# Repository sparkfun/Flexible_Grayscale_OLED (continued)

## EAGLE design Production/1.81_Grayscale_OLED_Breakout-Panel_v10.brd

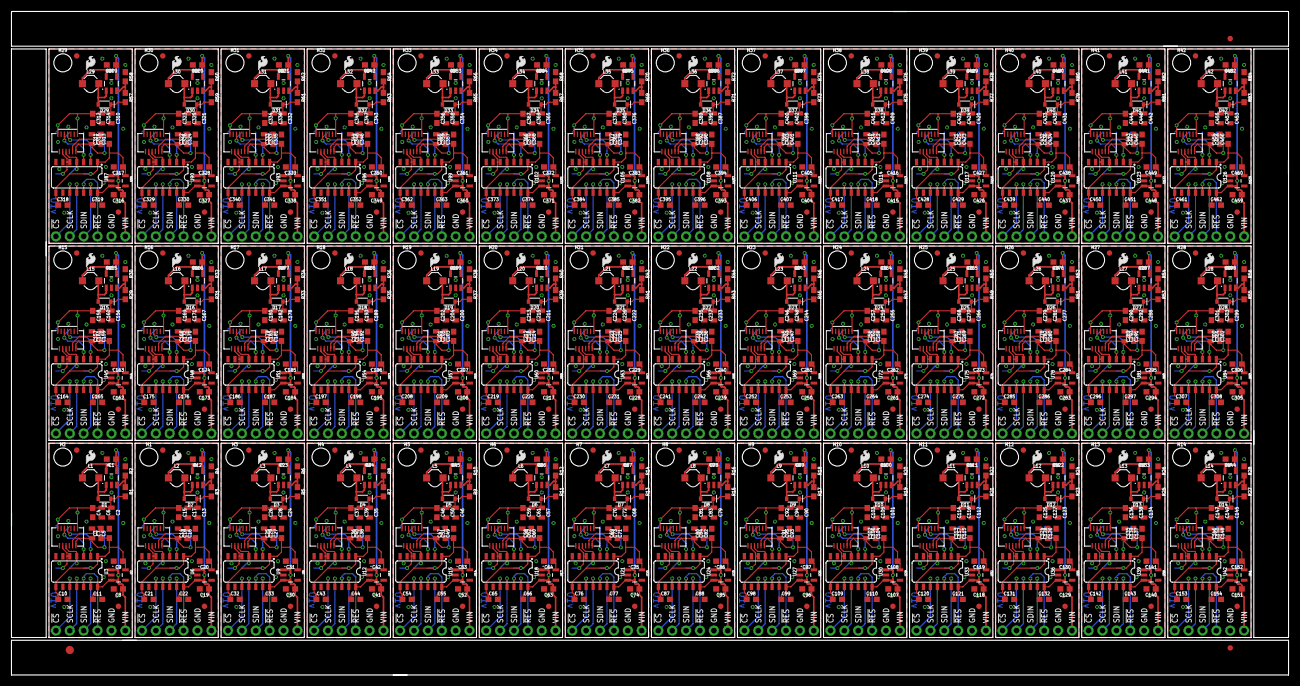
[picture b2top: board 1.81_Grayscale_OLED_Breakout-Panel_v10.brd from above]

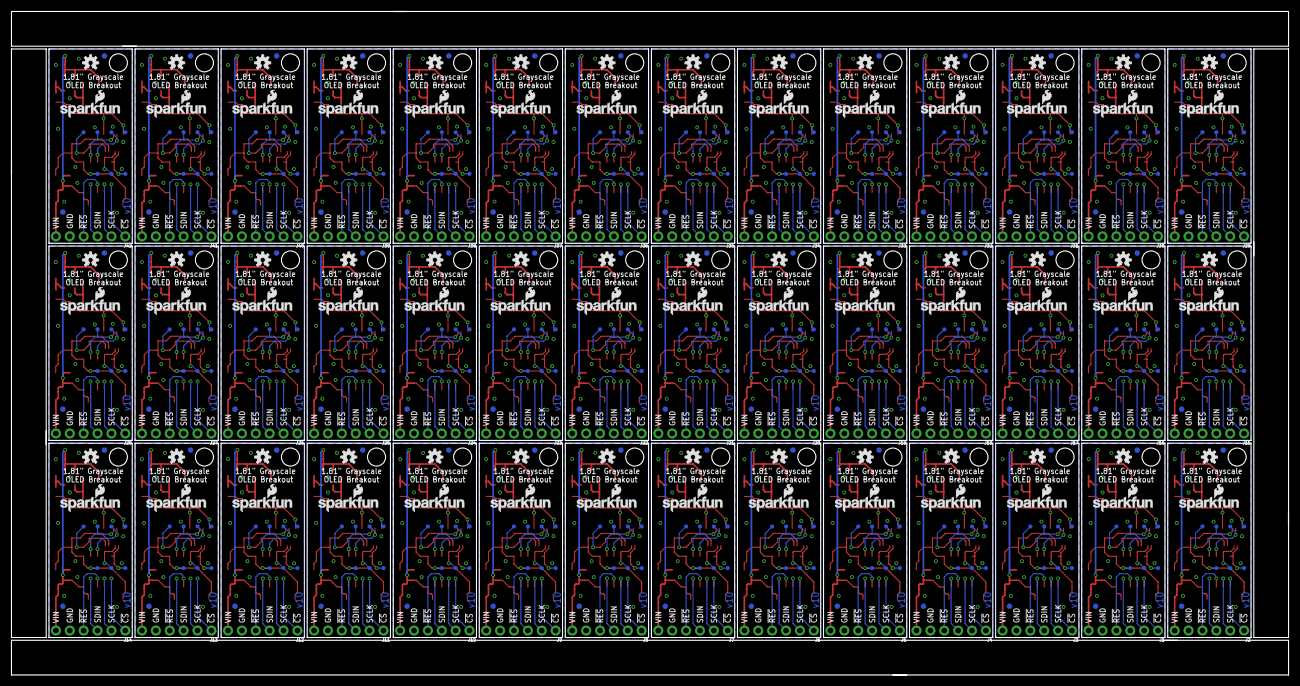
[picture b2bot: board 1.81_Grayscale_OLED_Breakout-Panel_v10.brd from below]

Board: 2 copper layers, 233.7 x 121.4 mm, 1473 parts (546 on the bottom side), 630 nets.

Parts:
C1, C5, C8, C12, C16, C19, C23, C27, C30, C34, C38, C41, C45, C49, C52, C56, C60, C63, C67, C71, C74, C78, C82, C85, C89, C93, C96, C100, C104, C107, C111, C115, C118, C122, C126, C129, C133, C137, C140, C144, C148, C151, C155, C159, C162, C166, C170, C173, C177, C181, C184, C188, C192, C195, C199, C203, C206, C210, C214, C217, C221, C225, C228, C232, C236, C239, C243, C247, C250, C254, C258, C261, C265, C269, C272, C276, C280, C283, C287, C291, C294, C298, C302, C305, C309, C313, C316, C320, C324, C327, C331, C335, C338, C342, C346, C349, C353, C357, C360, C364, C368, C371, C375, C379, C382, C386, C390, C393, C397, C401, C404, C408, C412, C415, C419, C423, C426, C430, C434, C437, C441, C445, C448, C452, C456, C459: 1.0uF; 0603
C2, C13, C24, C35, C46, C57, C68, C79, C90, C101, C112, C123, C134, C145, C156, C167, C178, C189, C200, C211, C222, C233, C244, C255, C266, C277, C288, C299, C310, C321, C332, C343, C354, C365, C376, C387, C398, C409, C420, C431, C442, C453: 1.0uF; 0805
C3, C10, C11, C14, C21, C22, C25, C32, C33, C36, C43, C44, C47, C54, C55, C58, C65, C66, C69, C76, C77, C80, C87, C88, C91, C98, C99, C102, C109, C110, C113, C120, C121, C124, C131, C132, C135, C142, C143, C146, C153, C154, C157, C164, C165, C168, C175, C176, C179, C186, C187, C190, C197, C198, C201, C208, C209, C212, C219, C220, C223, C230, C231, C234, C241, C242, C245, C252, C253, C256, C263, C264, C267, C274, C275, C278, C285, C286, C289, C296, C297, C300, C307, C308, C311, C318, C319, C322, C329, C330, C333, C340, C341, C344, C351, C352, C355, C362, C363, C366, C373, C374, C377, C384, C385, C388, C395, C396, C399, C406, C407, C410, C417, C418, C421, C428, C429, C432, C439, C440, C443, C450, C451, C454, C461, C462: 0.1uF; 0603
C4, C15, C26, C37, C48, C59, C70, C81, C92, C103, C114, C125, C136, C147, C158, C169, C180, C191, C202, C213, C224, C235, C246, C257, C268, C279, C290, C301, C312, C323, C334, C345, C356, C367, C378, C389, C400, C411, C422, C433, C444, C455: 0.1uF/25V; 0603
C6, C7, C17, C18, C28, C29, C39, C40, C50, C51, C61, C62, C72, C73, C83, C84, C94, C95, C105, C106, C116, C117, C127, C128, C138, C139, C149, C150, C160, C161, C171, C172, C182, C183, C193, C194, C204, C205, C215, C216, C226, C227, C237, C238, C248, C249, C259, C260, C270, C271, C281, C282, C292, C293, C303, C304, C314, C315, C325, C326, C336, C337, C347, C348, C358, C359, C369, C370, C380, C381, C391, C392, C402, C403, C413, C414, C424, C425, C435, C436, C446, C447, C457, C458: 2.2uF/25V; 0805
C9, C20, C31, C42, C53, C64, C75, C86, C97, C108, C119, C130, C141, C152, C163, C174, C185, C196, C207, C218, C229, C240, C251, C262, C273, C284, C295, C306, C317, C328, C339, C350, C361, C372, C383, C394, C405, C416, C427, C438, C449, C460: 2.2uF; 0603
D1, D2, D3, D4, D5, D6, D7, D8, D9, D10, D11, D12, D13, D14, D15, D16, D17, D18, D19, D20, D21, D22, D23, D24, D25, D26, D27, D28, D29, D30, D31, D32, D33, D34, D35, D36, D37, D38, D39, D40, D41, D42: 1A/23V/620mV; SOD-323
DS1, DS2, DS3, DS4, DS5, DS6, DS7, DS8, DS9, DS10, DS11, DS12, DS13, DS14, DS15, DS16, DS17, DS18, DS19, DS20, DS21, DS22, DS23, DS24, DS25, DS26, DS27, DS28, DS29, DS30, DS31, DS32, DS33, DS34, DS35, DS36, DS37, DS38, DS39, DS40, DS41, DS42: OEL_1.8OEL_Y3B; OEL_1.8_FPC_Y3B
E$1: FIDUCIAL-1.5X3
E$5, E$6: FIDUCIAL-1X2
FD1, FD2, FD3, FD4, FD5, FD6, FD7, FD8, FD9, FD10, FD11, FD12, FD13, FD14, FD15, FD16, FD17, FD18, FD19, FD20, FD21, FD22, FD23, FD24, FD25, FD26, FD27, FD28, FD29, FD30, FD31, FD32, FD33, FD34, FD35, FD36, FD37, FD38, FD39, FD40, FD41, FD42, FD43, FD44, FD45, FD46, FD47, FD48, FD49, FD50, FD51, FD52, FD53, FD54, FD55, FD56, FD57, FD58, FD59, FD60, FD61, FD62, FD63, FD64, FD65, FD66, FD67, FD68, FD69, FD70, FD71, FD72, FD73, FD74, FD75, FD76, FD77, FD78, FD79, FD80, FD81, FD82, FD83, FD84, FD85, FD86, FD87, FD88, FD89, FD90, FD91, FD92, FD93, FD94, FD95, FD96, FD97, FD98, FD99, FD100, FD101, FD102, FD103, FD104, FD105, FD106, FD107, FD108, FD109, FD110, FD111, FD112, FD113, FD114, FD115, FD116, FD117, FD118, FD119, FD120, FD121, FD122, FD123, FD124, FD125, FD126, FD127, FD128, FD129, FD130, FD131, FD132, FD133, FD134, FD135, FD136, FD137, FD138, FD139, FD140, FD141, FD142, FD143, FD144, FD145, FD146, FD147, FD148, FD149, FD150, FD151, FD152, FD153, FD154, FD155, FD156, FD157, FD158, FD159, FD160, FD161, FD162, FD163, FD164, FD165, FD166, FD167, FD168: FIDUCIAL1X2; FIDUCIAL-1X2
H1, H2, H3, H4, H5, H6, H7, H8, H9, H10, H11, H12, H13, H14, H15, H16, H17, H18, H19, H20, H21, H22, H23, H24, H25, H26, H27, H28, H29, H30, H31, H32, H33, H34, H35, H36, H37, H38, H39, H40, H41, H42: STAND-OFF
J1, J2, J3, J4, J5, J6, J7, J8, J9, J10, J11, J12, J13, J14, J15, J16, J17, J18, J19, J20, J21, J22, J23, J24, J25, J26, J27, J28, J29, J30, J31, J32, J33, J34, J35, J36, J37, J38, J39, J40, J41, J42: 1X06_NO_SILK
L1, L2, L3, L4, L5, L6, L7, L8, L9, L10, L11, L12, L13, L14, L15, L16, L17, L18, L19, L20, L21, L22, L23, L24, L25, L26, L27, L28, L29, L30, L31, L32, L33, L34, L35, L36, L37, L38, L39, L40, L41, L42: 10uH; INDUCTOR_4.7UH
LOGO1, LOGO2, LOGO7, LOGO10, LOGO13, LOGO16, LOGO19, LOGO22, LOGO25, LOGO28, LOGO31, LOGO34, LOGO37, LOGO40, LOGO43, LOGO46, LOGO49, LOGO52, LOGO55, LOGO58, LOGO61, LOGO64, LOGO67, LOGO70, LOGO73, LOGO76, LOGO79, LOGO82, LOGO85, LOGO88, LOGO91, LOGO94, LOGO97, LOGO100, LOGO103, LOGO106, LOGO109, LOGO112, LOGO115, LOGO118, LOGO121, LOGO124: SFE_LOGO_NAME_FLAME.1_INCH; SFE_LOGO_NAME_FLAME_.1
LOGO3, LOGO5, LOGO8, LOGO11, LOGO14, LOGO17, LOGO20, LOGO23, LOGO26, LOGO29, LOGO32, LOGO35, LOGO38, LOGO41, LOGO44, LOGO47, LOGO50, LOGO53, LOGO56, LOGO59, LOGO62, LOGO65, LOGO68, LOGO71, LOGO74, LOGO77, LOGO80, LOGO83, LOGO86, LOGO89, LOGO92, LOGO95, LOGO98, LOGO101, LOGO104, LOGO107, LOGO110, LOGO113, LOGO116, LOGO119, LOGO122, LOGO125: SFE_LOGO_FLAME.1_INCH; SFE_LOGO_FLAME_.1
LOGO4, LOGO6, LOGO9, LOGO12, LOGO15, LOGO18, LOGO21, LOGO24, LOGO27, LOGO30, LOGO33, LOGO36, LOGO39, LOGO42, LOGO45, LOGO48, LOGO51, LOGO54, LOGO57, LOGO60, LOGO63, LOGO66, LOGO69, LOGO72, LOGO75, LOGO78, LOGO81, LOGO84, LOGO87, LOGO90, LOGO93, LOGO96, LOGO99, LOGO102, LOGO105, LOGO108, LOGO111, LOGO114, LOGO117, LOGO120, LOGO123, LOGO126: OSHW-LOGOS; OSHW-LOGO-S
R1, R3, R5, R7, R9, R11, R13, R15, R17, R19, R21, R23, R25, R27, R29, R31, R33, R35, R37, R39, R41, R43, R45, R47, R49, R51, R53, R55, R57, R59, R61, R63, R65, R67, R69, R71, R73, R75, R77, R79, R81, R83: 47k; 0603
R2, R4, R6, R8, R10, R12, R14, R16, R18, R20, R22, R24, R26, R28, R30, R32, R34, R36, R38, R40, R42, R44, R46, R48, R50, R52, R54, R56, R58, R60, R62, R64, R66, R68, R70, R72, R74, R76, R78, R80, R82, R84: 5.6k; 0603
TP1, TP2, TP3, TP4, TP5, TP6, TP7, TP8, TP9, TP10, TP11, TP12, TP13, TP14, TP15, TP16, TP17, TP18, TP19, TP20, TP21, TP22, TP23, TP24, TP25, TP26, TP27, TP28, TP29, TP30, TP31, TP32, TP33, TP34, TP35, TP36, TP37, TP38, TP39, TP40, TP41, TP42, TP43, TP44, TP45, TP46, TP47, TP48, TP49, TP50, TP51, TP52, TP53, TP54, TP55, TP56, TP57, TP58, TP59, TP60, TP61, TP62, TP63, TP64, TP65, TP66, TP67, TP68, TP69, TP70, TP71, TP72, TP73, TP74, TP75, TP76, TP77, TP78, TP79, TP80, TP81, TP82, TP83, TP84, TP85, TP86, TP87, TP88, TP89, TP90, TP91, TP92, TP93, TP94, TP95, TP96, TP97, TP98, TP99, TP100, TP101, TP102, TP103, TP104, TP105, TP106, TP107, TP108, TP109, TP110, TP111, TP112, TP113, TP114, TP115, TP116, TP117, TP118, TP119, TP120, TP121, TP122, TP123, TP124, TP125, TP126, TP127, TP128, TP129, TP130, TP131, TP132, TP133, TP134, TP135, TP136, TP137, TP138, TP139, TP140, TP141, TP142, TP143, TP144, TP145, TP146, TP147, TP148, TP149, TP150, TP151, TP152, TP153, TP154, TP155, TP156, TP157, TP158, TP159, TP160, TP161, TP162, TP163, TP164, TP165, TP166, TP167, TP168, TP169, TP170, TP171, TP172, TP173, TP174, TP175, TP176, TP177, TP178, TP179, TP180, TP181, TP182, TP183, TP184, TP185, TP186, TP187, TP188, TP189, TP190, TP191, TP192, TP193, TP194, TP195, TP196, TP197, TP198, TP199, TP200, TP201, TP202, TP203, TP204, TP205, TP206, TP207, TP208, TP209, TP210, TP211, TP212, TP213, TP214, TP215, TP216, TP217, TP218, TP219, TP220, TP221, TP222, TP223, TP224, TP225, TP226, TP227, TP228, TP229, TP230, TP231, TP232, TP233, TP234, TP235, TP236, TP237, TP238, TP239, TP240, TP241, TP242, TP243, TP244, TP245, TP246, TP247, TP248, TP249, TP250, TP251, TP252, TP253, TP254, TP255, TP256, TP257, TP258, TP259, TP260, TP261, TP262, TP263, TP264, TP265, TP266, TP267, TP268, TP269, TP270, TP271, TP272, TP273, TP274, TP275, TP276, TP277, TP278, TP279, TP280, TP281, TP282, TP283, TP284, TP285, TP286, TP287, TP288, TP289, TP290, TP291, TP292, TP293, TP294: TEST-POINT3; PAD.03X.03
U1, U4, U7, U10, U13, U16, U19, U22, U25, U28, U31, U34, U37, U40, U43, U46, U49, U52, U55, U58, U61, U64, U67, U70, U73, U76, U79, U82, U85, U88, U91, U94, U97, U100, U103, U106, U109, U112, U115, U118, U121, U124: AP3012; SOT23-5
U2, U5, U8, U11, U14, U17, U20, U23, U26, U29, U32, U35, U38, U41, U44, U47, U50, U53, U56, U59, U62, U65, U68, U71, U74, U77, U80, U83, U86, U89, U92, U95, U98, U101, U104, U107, U110, U113, U116, U119, U122, U125: 3.3V; SOT23-5
U3, U6, U9, U12, U15, U18, U21, U24, U27, U30, U33, U36, U39, U42, U45, U48, U51, U54, U57, U60, U63, U66, U69, U72, U75, U78, U81, U84, U87, U90, U93, U96, U99, U102, U105, U108, U111, U114, U117, U120, U123, U126: TXB0104; SO14

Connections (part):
3.3V: C3.1, C5.1, C9.1, C10.1, DS1.10, TP6.P$1, U2.5, U3.1, U3.8
3.3V1: C14.1, C16.1, C20.1, C21.1, DS2.10, TP13.P$1, U5.5, U6.1, U6.8
3.3V2: C25.1, C27.1, C31.1, C32.1, DS3.10, TP20.P$1, U8.5, U9.1, U9.8
3.3V3: C36.1, C38.1, C42.1, C43.1, DS4.10, TP27.P$1, U11.5, U12.1, U12.8
3.3V4: C47.1, C49.1, C53.1, C54.1, DS5.10, TP34.P$1, U14.5, U15.1, U15.8
3.3V5: C58.1, C60.1, C64.1, C65.1, DS6.10, TP41.P$1, U17.5, U18.1, U18.8
3.3V6: C69.1, C71.1, C75.1, C76.1, DS7.10, TP48.P$1, U20.5, U21.1, U21.8
3.3V7: C80.1, C82.1, C86.1, C87.1, DS8.10, TP55.P$1, U23.5, U24.1, U24.8
3.3V8: C91.1, C93.1, C97.1, C98.1, DS9.10, TP62.P$1, U26.5, U27.1, U27.8
3.3V9: C102.1, C104.1, C108.1, C109.1, DS10.10, TP69.P$1, U29.5, U30.1, U30.8
3.3V10: C113.1, C115.1, C119.1, C120.1, DS11.10, TP76.P$1, U32.5, U33.1, U33.8
3.3V11: C124.1, C126.1, C130.1, C131.1, DS12.10, TP83.P$1, U35.5, U36.1, U36.8
3.3V12: C135.1, C137.1, C141.1, C142.1, DS13.10, TP90.P$1, U38.5, U39.1, U39.8
3.3V13: C146.1, C148.1, C152.1, C153.1, DS14.10, TP97.P$1, U41.5, U42.1, U42.8
3.3V14: C157.1, C159.1, C163.1, C164.1, DS15.10, TP104.P$1, U44.5, U45.1, U45.8
3.3V15: C168.1, C170.1, C174.1, C175.1, DS16.10, TP111.P$1, U47.5, U48.1, U48.8
3.3V16: C179.1, C181.1, C185.1, C186.1, DS17.10, TP118.P$1, U50.5, U51.1, U51.8
3.3V17: C190.1, C192.1, C196.1, C197.1, DS18.10, TP125.P$1, U53.5, U54.1, U54.8
3.3V18: C201.1, C203.1, C207.1, C208.1, DS19.10, TP132.P$1, U56.5, U57.1, U57.8
3.3V19: C212.1, C214.1, C218.1, C219.1, DS20.10, TP139.P$1, U59.5, U60.1, U60.8
3.3V20: C223.1, C225.1, C229.1, C230.1, DS21.10, TP146.P$1, U62.5, U63.1, U63.8
3.3V21: C234.1, C236.1, C240.1, C241.1, DS22.10, TP153.P$1, U65.5, U66.1, U66.8
3.3V22: C245.1, C247.1, C251.1, C252.1, DS23.10, TP160.P$1, U68.5, U69.1, U69.8
3.3V23: C256.1, C258.1, C262.1, C263.1, DS24.10, TP167.P$1, U71.5, U72.1, U72.8
3.3V24: C267.1, C269.1, C273.1, C274.1, DS25.10, TP174.P$1, U74.5, U75.1, U75.8
3.3V25: C278.1, C280.1, C284.1, C285.1, DS26.10, TP181.P$1, U77.5, U78.1, U78.8
3.3V26: C289.1, C291.1, C295.1, C296.1, DS27.10, TP188.P$1, U80.5, U81.1, U81.8
3.3V27: C300.1, C302.1, C306.1, C307.1, DS28.10, TP195.P$1, U83.5, U84.1, U84.8
3.3V28: C311.1, C313.1, C317.1, C318.1, DS29.10, TP202.P$1, U86.5, U87.1, U87.8
3.3V29: C322.1, C324.1, C328.1, C329.1, DS30.10, TP209.P$1, U89.5, U90.1, U90.8
3.3V30: C333.1, C335.1, C339.1, C340.1, DS31.10, TP216.P$1, U92.5, U93.1, U93.8
3.3V31: C344.1, C346.1, C350.1, C351.1, DS32.10, TP223.P$1, U95.5, U96.1, U96.8
3.3V32: C355.1, C357.1, C361.1, C362.1, DS33.10, TP230.P$1, U98.5, U99.1, U99.8
3.3V33: C366.1, C368.1, C372.1, C373.1, DS34.10, TP237.P$1, U101.5, U102.1, U102.8
3.3V34: C377.1, C379.1, C383.1, C384.1, DS35.10, TP244.P$1, U104.5, U105.1, U105.8
3.3V35: C388.1, C390.1, C394.1, C395.1, DS36.10, TP251.P$1, U107.5, U108.1, U108.8
3.3V36: C399.1, C401.1, C405.1, C406.1, DS37.10, TP258.P$1, U110.5, U111.1, U111.8
3.3V37: C410.1, C412.1, C416.1, C417.1, DS38.10, TP265.P$1, U113.5, U114.1, U114.8
3.3V38: C421.1, C423.1, C427.1, C428.1, DS39.10, TP272.P$1, U116.5, U117.1, U117.8
3.3V39: C432.1, C434.1, C438.1, C439.1, DS40.10, TP279.P$1, U119.5, U120.1, U120.8
3.3V40: C443.1, C445.1, C449.1, C450.1, DS41.10, TP286.P$1, U122.5, U123.1, U123.8
3.3V41: C454.1, C456.1, C460.1, C461.1, DS42.10, TP293.P$1, U125.5, U126.1, U126.8
12V: C2.1, C4.1, C6.1, D1.C, DS1.1, DS1.13, R1.2, TP7.P$1
12V1: C13.1, C15.1, C17.1, D2.C, DS2.1, DS2.13, R3.2, TP14.P$1
12V2: C24.1, C26.1, C28.1, D3.C, DS3.1, DS3.13, R5.2, TP21.P$1
12V3: C35.1, C37.1, C39.1, D4.C, DS4.1, DS4.13, R7.2, TP28.P$1
12V4: C46.1, C48.1, C50.1, D5.C, DS5.1, DS5.13, R9.2, TP35.P$1
12V5: C57.1, C59.1, C61.1, D6.C, DS6.1, DS6.13, R11.2, TP42.P$1
12V6: C68.1, C70.1, C72.1, D7.C, DS7.1, DS7.13, R13.2, TP49.P$1
12V7: C79.1, C81.1, C83.1, D8.C, DS8.1, DS8.13, R15.2, TP56.P$1
12V8: C90.1, C92.1, C94.1, D9.C, DS9.1, DS9.13, R17.2, TP63.P$1
12V9: C101.1, C103.1, C105.1, D10.C, DS10.1, DS10.13, R19.2, TP70.P$1
12V10: C112.1, C114.1, C116.1, D11.C, DS11.1, DS11.13, R21.2, TP77.P$1
12V11: C123.1, C125.1, C127.1, D12.C, DS12.1, DS12.13, R23.2, TP84.P$1
12V12: C134.1, C136.1, C138.1, D13.C, DS13.1, DS13.13, R25.2, TP91.P$1
12V13: C145.1, C147.1, C149.1, D14.C, DS14.1, DS14.13, R27.2, TP98.P$1
12V14: C156.1, C158.1, C160.1, D15.C, DS15.1, DS15.13, R29.2, TP105.P$1
12V15: C167.1, C169.1, C171.1, D16.C, DS16.1, DS16.13, R31.2, TP112.P$1
12V16: C178.1, C180.1, C182.1, D17.C, DS17.1, DS17.13, R33.2, TP119.P$1
12V17: C189.1, C191.1, C193.1, D18.C, DS18.1, DS18.13, R35.2, TP126.P$1
12V18: C200.1, C202.1, C204.1, D19.C, DS19.1, DS19.13, R37.2, TP133.P$1
12V19: C211.1, C213.1, C215.1, D20.C, DS20.1, DS20.13, R39.2, TP140.P$1
12V20: C222.1, C224.1, C226.1, D21.C, DS21.1, DS21.13, R41.2, TP147.P$1
12V21: C233.1, C235.1, C237.1, D22.C, DS22.1, DS22.13, R43.2, TP154.P$1
12V22: C244.1, C246.1, C248.1, D23.C, DS23.1, DS23.13, R45.2, TP161.P$1
12V23: C255.1, C257.1, C259.1, D24.C, DS24.1, DS24.13, R47.2, TP168.P$1
12V24: C266.1, C268.1, C270.1, D25.C, DS25.1, DS25.13, R49.2, TP175.P$1
12V25: C277.1, C279.1, C281.1, D26.C, DS26.1, DS26.13, R51.2, TP182.P$1
12V26: C288.1, C290.1, C292.1, D27.C, DS27.1, DS27.13, R53.2, TP189.P$1
12V27: C299.1, C301.1, C303.1, D28.C, DS28.1, DS28.13, R55.2, TP196.P$1
12V28: C310.1, C312.1, C314.1, D29.C, DS29.1, DS29.13, R57.2, TP203.P$1
12V29: C321.1, C323.1, C325.1, D30.C, DS30.1, DS30.13, R59.2, TP210.P$1
12V30: C332.1, C334.1, C336.1, D31.C, DS31.1, DS31.13, R61.2, TP217.P$1
12V31: C343.1, C345.1, C347.1, D32.C, DS32.1, DS32.13, R63.2, TP224.P$1
12V32: C354.1, C356.1, C358.1, D33.C, DS33.1, DS33.13, R65.2, TP231.P$1
12V33: C365.1, C367.1, C369.1, D34.C, DS34.1, DS34.13, R67.2, TP238.P$1
12V34: C376.1, C378.1, C380.1, D35.C, DS35.1, DS35.13, R69.2, TP245.P$1
12V35: C387.1, C389.1, C391.1, D36.C, DS36.1, DS36.13, R71.2, TP252.P$1
12V36: C398.1, C400.1, C402.1, D37.C, DS37.1, DS37.13, R73.2, TP259.P$1
12V37: C409.1, C411.1, C413.1, D38.C, DS38.1, DS38.13, R75.2, TP266.P$1
12V38: C420.1, C422.1, C424.1, D39.C, DS39.1, DS39.13, R77.2, TP273.P$1
12V39: C431.1, C433.1, C435.1, D40.C, DS40.1, DS40.13, R79.2, TP280.P$1
12V40: C442.1, C444.1, C446.1, D41.C, DS41.1, DS41.13, R81.2, TP287.P$1
12V41: C453.1, C455.1, C457.1, D42.C, DS42.1, DS42.13, R83.2, TP294.P$1
!CS!: DS1.4, TP2.P$1, U3.5
!CS!1: DS2.4, TP9.P$1, U6.5
!CS!2: DS3.4, TP16.P$1, U9.5
!CS!3: DS4.4, TP23.P$1, U12.5
!CS!4: DS5.4, TP30.P$1, U15.5
!CS!5: DS6.4, TP37.P$1, U18.5
!CS!6: DS7.4, TP44.P$1, U21.5
!CS!7: DS8.4, TP51.P$1, U24.5
!CS!8: DS9.4, TP58.P$1, U27.5
!CS!9: DS10.4, TP65.P$1, U30.5
!CS!10: DS11.4, TP72.P$1, U33.5
!CS!11: DS12.4, TP79.P$1, U36.5
!CS!12: DS13.4, TP86.P$1, U39.5
!CS!13: DS14.4, TP93.P$1, U42.5
!CS!14: DS15.4, TP100.P$1, U45.5
!CS!15: DS16.4, TP107.P$1, U48.5
!CS!16: DS17.4, TP114.P$1, U51.5
!CS!17: DS18.4, TP121.P$1, U54.5
!CS!18: DS19.4, TP128.P$1, U57.5
!CS!19: DS20.4, TP135.P$1, U60.5
!CS!20: DS21.4, TP142.P$1, U63.5
!CS!21: DS22.4, TP149.P$1, U66.5
!CS!22: DS23.4, TP156.P$1, U69.5
!CS!23: DS24.4, TP163.P$1, U72.5
!CS!24: DS25.4, TP170.P$1, U75.5
!CS!25: DS26.4, TP177.P$1, U78.5
!CS!26: DS27.4, TP184.P$1, U81.5
!CS!27: DS28.4, TP191.P$1, U84.5
!CS!28: DS29.4, TP198.P$1, U87.5
!CS!29: DS30.4, TP205.P$1, U90.5
!CS!30: DS31.4, TP212.P$1, U93.5
!CS!31: DS32.4, TP219.P$1, U96.5
!CS!32: DS33.4, TP226.P$1, U99.5
!CS!33: DS34.4, TP233.P$1, U102.5
!CS!34: DS35.4, TP240.P$1, U105.5
!CS!35: DS36.4, TP247.P$1, U108.5
!CS!36: DS37.4, TP254.P$1, U111.5
!CS!37: DS38.4, TP261.P$1, U114.5
!CS!38: DS39.4, TP268.P$1, U117.5
!CS!39: DS40.4, TP275.P$1, U120.5
!CS!40: DS41.4, TP282.P$1, U123.5
!CS!41: DS42.4, TP289.P$1, U126.5
!CS!_HIGH: J2.1, U3.10
!CS!_HIGH1: J1.1, U6.10
!CS!_HIGH2: J3.1, U9.10
!CS!_HIGH3: J4.1, U12.10
!CS!_HIGH4: J5.1, U15.10
!CS!_HIGH5: J6.1, U18.10
!CS!_HIGH6: J7.1, U21.10
!CS!_HIGH7: J8.1, U24.10
!CS!_HIGH8: J9.1, U27.10
!CS!_HIGH9: J10.1, U30.10
!CS!_HIGH10: J11.1, U33.10
!CS!_HIGH11: J12.1, U36.10
!CS!_HIGH12: J13.1, U39.10
!CS!_HIGH13: J14.1, U42.10
!CS!_HIGH14: J15.1, U45.10
!CS!_HIGH15: J16.1, U48.10
!CS!_HIGH16: J17.1, U51.10
!CS!_HIGH17: J18.1, U54.10
!CS!_HIGH18: J19.1, U57.10
!CS!_HIGH19: J20.1, U60.10
!CS!_HIGH20: J21.1, U63.10
!CS!_HIGH21: J22.1, U66.10
!CS!_HIGH22: J23.1, U69.10
!CS!_HIGH23: J24.1, U72.10
!CS!_HIGH24: J25.1, U75.10
!CS!_HIGH25: J26.1, U78.10
!CS!_HIGH26: J27.1, U81.10
!CS!_HIGH27: J28.1, U84.10
!CS!_HIGH28: J29.1, U87.10
!CS!_HIGH29: J30.1, U90.10
!CS!_HIGH30: J31.1, U93.10
!CS!_HIGH31: J32.1, U96.10
!CS!_HIGH32: J33.1, U99.10
!CS!_HIGH33: J34.1, U102.10
!CS!_HIGH34: J35.1, U105.10
!CS!_HIGH35: J36.1, U108.10
!CS!_HIGH36: J37.1, U111.10
!CS!_HIGH37: J38.1, U114.10
!CS!_HIGH38: J39.1, U117.10
!CS!_HIGH39: J40.1, U120.10
!CS!_HIGH40: J41.1, U123.10
!CS!_HIGH41: J42.1, U126.10
!RES!: DS1.5, TP1.P$1, U3.3
!RES!1: DS2.5, TP8.P$1, U6.3
!RES!2: DS3.5, TP15.P$1, U9.3
!RES!3: DS4.5, TP22.P$1, U12.3
!RES!4: DS5.5, TP29.P$1, U15.3
!RES!5: DS6.5, TP36.P$1, U18.3
!RES!6: DS7.5, TP43.P$1, U21.3
!RES!7: DS8.5, TP50.P$1, U24.3
!RES!8: DS9.5, TP57.P$1, U27.3
!RES!9: DS10.5, TP64.P$1, U30.3
!RES!10: DS11.5, TP71.P$1, U33.3
!RES!11: DS12.5, TP78.P$1, U36.3
!RES!12: DS13.5, TP85.P$1, U39.3
!RES!13: DS14.5, TP92.P$1, U42.3
!RES!14: DS15.5, TP99.P$1, U45.3
!RES!15: DS16.5, TP106.P$1, U48.3
!RES!16: DS17.5, TP113.P$1, U51.3
!RES!17: DS18.5, TP120.P$1, U54.3
!RES!18: DS19.5, TP127.P$1, U57.3
!RES!19: DS20.5, TP134.P$1, U60.3
!RES!20: DS21.5, TP141.P$1, U63.3
!RES!21: DS22.5, TP148.P$1, U66.3
!RES!22: DS23.5, TP155.P$1, U69.3
!RES!23: DS24.5, TP162.P$1, U72.3
!RES!24: DS25.5, TP169.P$1, U75.3
!RES!25: DS26.5, TP176.P$1, U78.3
!RES!26: DS27.5, TP183.P$1, U81.3
!RES!27: DS28.5, TP190.P$1, U84.3
!RES!28: DS29.5, TP197.P$1, U87.3
!RES!29: DS30.5, TP204.P$1, U90.3
!RES!30: DS31.5, TP211.P$1, U93.3
!RES!31: DS32.5, TP218.P$1, U96.3
!RES!32: DS33.5, TP225.P$1, U99.3
!RES!33: DS34.5, TP232.P$1, U102.3
!RES!34: DS35.5, TP239.P$1, U105.3
!RES!35: DS36.5, TP246.P$1, U108.3
!RES!36: DS37.5, TP253.P$1, U111.3
!RES!37: DS38.5, TP260.P$1, U114.3
!RES!38: DS39.5, TP267.P$1, U117.3
!RES!39: DS40.5, TP274.P$1, U120.3
!RES!40: DS41.5, TP281.P$1, U123.3
!RES!41: DS42.5, TP288.P$1, U126.3
!RES!_HIGH: J2.4, U3.12
!RES!_HIGH1: J1.4, U6.12
!RES!_HIGH2: J3.4, U9.12
!RES!_HIGH3: J4.4, U12.12
!RES!_HIGH4: J5.4, U15.12
!RES!_HIGH5: J6.4, U18.12
!RES!_HIGH6: J7.4, U21.12
!RES!_HIGH7: J8.4, U24.12
!RES!_HIGH8: J9.4, U27.12
!RES!_HIGH9: J10.4, U30.12
!RES!_HIGH10: J11.4, U33.12
!RES!_HIGH11: J12.4, U36.12
!RES!_HIGH12: J13.4, U39.12
!RES!_HIGH13: J14.4, U42.12
!RES!_HIGH14: J15.4, U45.12
!RES!_HIGH15: J16.4, U48.12
!RES!_HIGH16: J17.4, U51.12
!RES!_HIGH17: J18.4, U54.12
!RES!_HIGH18: J19.4, U57.12
!RES!_HIGH19: J20.4, U60.12
!RES!_HIGH20: J21.4, U63.12
!RES!_HIGH21: J22.4, U66.12
!RES!_HIGH22: J23.4, U69.12
!RES!_HIGH23: J24.4, U72.12
!RES!_HIGH24: J25.4, U75.12
!RES!_HIGH25: J26.4, U78.12
!RES!_HIGH26: J27.4, U81.12
!RES!_HIGH27: J28.4, U84.12
!RES!_HIGH28: J29.4, U87.12
!RES!_HIGH29: J30.4, U90.12
!RES!_HIGH30: J31.4, U93.12
!RES!_HIGH31: J32.4, U96.12
!RES!_HIGH32: J33.4, U99.12
!RES!_HIGH33: J34.4, U102.12
!RES!_HIGH34: J35.4, U105.12
!RES!_HIGH35: J36.4, U108.12
!RES!_HIGH36: J37.4, U111.12
!RES!_HIGH37: J38.4, U114.12
!RES!_HIGH38: J39.4, U117.12
!RES!_HIGH39: J40.4, U120.12
!RES!_HIGH40: J41.4, U123.12
!RES!_HIGH41: J42.4, U126.12
GND: C1.2, C2.2, C3.2, C4.2, C5.2, C6.2, C7.1, C8.2, C9.2, C10.2, C11.2, DS1.2, DS1.3, DS1.8, DS1.9, J2.5, R2.1, U1.2, U2.2, U3.7
GND1: C12.2, C13.2, C14.2, C15.2, C16.2, C17.2, C18.1, C19.2, C20.2, C21.2, C22.2, DS2.2, DS2.3, DS2.8, DS2.9, J1.5, R4.1, U4.2, U5.2, U6.7
GND2: C23.2, C24.2, C25.2, C26.2, C27.2, C28.2, C29.1, C30.2, C31.2, C32.2, C33.2, DS3.2, DS3.3, DS3.8, DS3.9, J3.5, R6.1, U7.2, U8.2, U9.7
GND3: C34.2, C35.2, C36.2, C37.2, C38.2, C39.2, C40.1, C41.2, C42.2, C43.2, C44.2, DS4.2, DS4.3, DS4.8, DS4.9, J4.5, R8.1, U10.2, U11.2, U12.7
GND4: C45.2, C46.2, C47.2, C48.2, C49.2, C50.2, C51.1, C52.2, C53.2, C54.2, C55.2, DS5.2, DS5.3, DS5.8, DS5.9, J5.5, R10.1, U13.2, U14.2, U15.7
GND5: C56.2, C57.2, C58.2, C59.2, C60.2, C61.2, C62.1, C63.2, C64.2, C65.2, C66.2, DS6.2, DS6.3, DS6.8, DS6.9, J6.5, R12.1, U16.2, U17.2, U18.7
GND6: C67.2, C68.2, C69.2, C70.2, C71.2, C72.2, C73.1, C74.2, C75.2, C76.2, C77.2, DS7.2, DS7.3, DS7.8, DS7.9, J7.5, R14.1, U19.2, U20.2, U21.7
GND7: C78.2, C79.2, C80.2, C81.2, C82.2, C83.2, C84.1, C85.2, C86.2, C87.2, C88.2, DS8.2, DS8.3, DS8.8, DS8.9, J8.5, R16.1, U22.2, U23.2, U24.7
GND8: C89.2, C90.2, C91.2, C92.2, C93.2, C94.2, C95.1, C96.2, C97.2, C98.2, C99.2, DS9.2, DS9.3, DS9.8, DS9.9, J9.5, R18.1, U25.2, U26.2, U27.7
GND9: C100.2, C101.2, C102.2, C103.2, C104.2, C105.2, C106.1, C107.2, C108.2, C109.2, C110.2, DS10.2, DS10.3, DS10.8, DS10.9, J10.5, R20.1, U28.2, U29.2, U30.7
GND10: C111.2, C112.2, C113.2, C114.2, C115.2, C116.2, C117.1, C118.2, C119.2, C120.2, C121.2, DS11.2, DS11.3, DS11.8, DS11.9, J11.5, R22.1, U31.2, U32.2, U33.7
GND11: C122.2, C123.2, C124.2, C125.2, C126.2, C127.2, C128.1, C129.2, C130.2, C131.2, C132.2, DS12.2, DS12.3, DS12.8, DS12.9, J12.5, R24.1, U34.2, U35.2, U36.7
GND12: C133.2, C134.2, C135.2, C136.2, C137.2, C138.2, C139.1, C140.2, C141.2, C142.2, C143.2, DS13.2, DS13.3, DS13.8, DS13.9, J13.5, R26.1, U37.2, U38.2, U39.7
GND13: C144.2, C145.2, C146.2, C147.2, C148.2, C149.2, C150.1, C151.2, C152.2, C153.2, C154.2, DS14.2, DS14.3, DS14.8, DS14.9, J14.5, R28.1, U40.2, U41.2, U42.7
GND14: C155.2, C156.2, C157.2, C158.2, C159.2, C160.2, C161.1, C162.2, C163.2, C164.2, C165.2, DS15.2, DS15.3, DS15.8, DS15.9, J15.5, R30.1, U43.2, U44.2, U45.7
GND15: C166.2, C167.2, C168.2, C169.2, C170.2, C171.2, C172.1, C173.2, C174.2, C175.2, C176.2, DS16.2, DS16.3, DS16.8, DS16.9, J16.5, R32.1, U46.2, U47.2, U48.7
GND16: C177.2, C178.2, C179.2, C180.2, C181.2, C182.2, C183.1, C184.2, C185.2, C186.2, C187.2, DS17.2, DS17.3, DS17.8, DS17.9, J17.5, R34.1, U49.2, U50.2, U51.7
GND17: C188.2, C189.2, C190.2, C191.2, C192.2, C193.2, C194.1, C195.2, C196.2, C197.2, C198.2, DS18.2, DS18.3, DS18.8, DS18.9, J18.5, R36.1, U52.2, U53.2, U54.7
GND18: C199.2, C200.2, C201.2, C202.2, C203.2, C204.2, C205.1, C206.2, C207.2, C208.2, C209.2, DS19.2, DS19.3, DS19.8, DS19.9, J19.5, R38.1, U55.2, U56.2, U57.7
GND19: C210.2, C211.2, C212.2, C213.2, C214.2, C215.2, C216.1, C217.2, C218.2, C219.2, C220.2, DS20.2, DS20.3, DS20.8, DS20.9, J20.5, R40.1, U58.2, U59.2, U60.7
GND20: C221.2, C222.2, C223.2, C224.2, C225.2, C226.2, C227.1, C228.2, C229.2, C230.2, C231.2, DS21.2, DS21.3, DS21.8, DS21.9, J21.5, R42.1, U61.2, U62.2, U63.7
GND21: C232.2, C233.2, C234.2, C235.2, C236.2, C237.2, C238.1, C239.2, C240.2, C241.2, C242.2, DS22.2, DS22.3, DS22.8, DS22.9, J22.5, R44.1, U64.2, U65.2, U66.7
GND22: C243.2, C244.2, C245.2, C246.2, C247.2, C248.2, C249.1, C250.2, C251.2, C252.2, C253.2, DS23.2, DS23.3, DS23.8, DS23.9, J23.5, R46.1, U67.2, U68.2, U69.7
GND23: C254.2, C255.2, C256.2, C257.2, C258.2, C259.2, C260.1, C261.2, C262.2, C263.2, C264.2, DS24.2, DS24.3, DS24.8, DS24.9, J24.5, R48.1, U70.2, U71.2, U72.7
GND24: C265.2, C266.2, C267.2, C268.2, C269.2, C270.2, C271.1, C272.2, C273.2, C274.2, C275.2, DS25.2, DS25.3, DS25.8, DS25.9, J25.5, R50.1, U73.2, U74.2, U75.7
GND25: C276.2, C277.2, C278.2, C279.2, C280.2, C281.2, C282.1, C283.2, C284.2, C285.2, C286.2, DS26.2, DS26.3, DS26.8, DS26.9, J26.5, R52.1, U76.2, U77.2, U78.7
GND26: C287.2, C288.2, C289.2, C290.2, C291.2, C292.2, C293.1, C294.2, C295.2, C296.2, C297.2, DS27.2, DS27.3, DS27.8, DS27.9, J27.5, R54.1, U79.2, U80.2, U81.7
GND27: C298.2, C299.2, C300.2, C301.2, C302.2, C303.2, C304.1, C305.2, C306.2, C307.2, C308.2, DS28.2, DS28.3, DS28.8, DS28.9, J28.5, R56.1, U82.2, U83.2, U84.7
GND28: C309.2, C310.2, C311.2, C312.2, C313.2, C314.2, C315.1, C316.2, C317.2, C318.2, C319.2, DS29.2, DS29.3, DS29.8, DS29.9, J29.5, R58.1, U85.2, U86.2, U87.7
GND29: C320.2, C321.2, C322.2, C323.2, C324.2, C325.2, C326.1, C327.2, C328.2, C329.2, C330.2, DS30.2, DS30.3, DS30.8, DS30.9, J30.5, R60.1, U88.2, U89.2, U90.7
GND30: C331.2, C332.2, C333.2, C334.2, C335.2, C336.2, C337.1, C338.2, C339.2, C340.2, C341.2, DS31.2, DS31.3, DS31.8, DS31.9, J31.5, R62.1, U91.2, U92.2, U93.7
GND31: C342.2, C343.2, C344.2, C345.2, C346.2, C347.2, C348.1, C349.2, C350.2, C351.2, C352.2, DS32.2, DS32.3, DS32.8, DS32.9, J32.5, R64.1, U94.2, U95.2, U96.7
GND32: C353.2, C354.2, C355.2, C356.2, C357.2, C358.2, C359.1, C360.2, C361.2, C362.2, C363.2, DS33.2, DS33.3, DS33.8, DS33.9, J33.5, R66.1, U97.2, U98.2, U99.7
GND33: C364.2, C365.2, C366.2, C367.2, C368.2, C369.2, C370.1, C371.2, C372.2, C373.2, C374.2, DS34.2, DS34.3, DS34.8, DS34.9, J34.5, R68.1, U100.2, U101.2, U102.7
GND34: C375.2, C376.2, C377.2, C378.2, C379.2, C380.2, C381.1, C382.2, C383.2, C384.2, C385.2, DS35.2, DS35.3, DS35.8, DS35.9, J35.5, R70.1, U103.2, U104.2, U105.7
GND35: C386.2, C387.2, C388.2, C389.2, C390.2, C391.2, C392.1, C393.2, C394.2, C395.2, C396.2, DS36.2, DS36.3, DS36.8, DS36.9, J36.5, R72.1, U106.2, U107.2, U108.7
GND36: C397.2, C398.2, C399.2, C400.2, C401.2, C402.2, C403.1, C404.2, C405.2, C406.2, C407.2, DS37.2, DS37.3, DS37.8, DS37.9, J37.5, R74.1, U109.2, U110.2, U111.7
GND37: C408.2, C409.2, C410.2, C411.2, C412.2, C413.2, C414.1, C415.2, C416.2, C417.2, C418.2, DS38.2, DS38.3, DS38.8, DS38.9, J38.5, R76.1, U112.2, U113.2, U114.7
GND38: C419.2, C420.2, C421.2, C422.2, C423.2, C424.2, C425.1, C426.2, C427.2, C428.2, C429.2, DS39.2, DS39.3, DS39.8, DS39.9, J39.5, R78.1, U115.2, U116.2, U117.7
GND39: C430.2, C431.2, C432.2, C433.2, C434.2, C435.2, C436.1, C437.2, C438.2, C439.2, C440.2, DS40.2, DS40.3, DS40.8, DS40.9, J40.5, R80.1, U118.2, U119.2, U120.7
GND40: C441.2, C442.2, C443.2, C444.2, C445.2, C446.2, C447.1, C448.2, C449.2, C450.2, C451.2, DS41.2, DS41.3, DS41.8, DS41.9, J41.5, R82.1, U121.2, U122.2, U123.7
GND41: C452.2, C453.2, C454.2, C455.2, C456.2, C457.2, C458.1, C459.2, C460.2, C461.2, C462.2, DS42.2, DS42.3, DS42.8, DS42.9, J42.5, R84.1, U124.2, U125.2, U126.7
unnamed: C7.2, DS1.12, TP5.P$1
unnamed: D1.A, L1.P$2, U1.1
unnamed: R1.1, R2.2, U1.3
unnamed: D2.A, L2.P$2, U4.1
unnamed: R3.1, R4.2, U4.3
unnamed: C18.2, DS2.12, TP12.P$1
unnamed: D3.A, L3.P$2, U7.1
unnamed: R5.1, R6.2, U7.3
unnamed: C29.2, DS3.12, TP19.P$1
unnamed: D4.A, L4.P$2, U10.1
unnamed: R7.1, R8.2, U10.3
unnamed: C40.2, DS4.12, TP26.P$1
unnamed: D5.A, L5.P$2, U13.1
unnamed: R9.1, R10.2, U13.3
unnamed: C51.2, DS5.12, TP33.P$1
unnamed: D6.A, L6.P$2, U16.1
unnamed: R11.1, R12.2, U16.3
unnamed: C62.2, DS6.12, TP40.P$1
unnamed: D7.A, L7.P$2, U19.1
unnamed: R13.1, R14.2, U19.3
unnamed: C73.2, DS7.12, TP47.P$1
unnamed: D8.A, L8.P$2, U22.1
unnamed: R15.1, R16.2, U22.3
unnamed: C84.2, DS8.12, TP54.P$1
unnamed: D9.A, L9.P$2, U25.1
unnamed: R17.1, R18.2, U25.3
unnamed: C95.2, DS9.12, TP61.P$1
unnamed: D10.A, L10.P$2, U28.1
unnamed: R19.1, R20.2, U28.3
unnamed: C106.2, DS10.12, TP68.P$1
unnamed: D11.A, L11.P$2, U31.1
unnamed: R21.1, R22.2, U31.3
unnamed: C117.2, DS11.12, TP75.P$1
unnamed: D12.A, L12.P$2, U34.1
unnamed: R23.1, R24.2, U34.3
unnamed: C128.2, DS12.12, TP82.P$1
unnamed: D13.A, L13.P$2, U37.1
unnamed: R25.1, R26.2, U37.3
unnamed: C139.2, DS13.12, TP89.P$1
unnamed: D14.A, L14.P$2, U40.1
unnamed: R27.1, R28.2, U40.3
unnamed: C150.2, DS14.12, TP96.P$1
unnamed: D15.A, L15.P$2, U43.1
unnamed: R29.1, R30.2, U43.3
unnamed: C161.2, DS15.12, TP103.P$1
unnamed: D16.A, L16.P$2, U46.1
unnamed: R31.1, R32.2, U46.3
unnamed: C172.2, DS16.12, TP110.P$1
unnamed: D17.A, L17.P$2, U49.1
unnamed: R33.1, R34.2, U49.3
unnamed: C183.2, DS17.12, TP117.P$1
unnamed: D18.A, L18.P$2, U52.1
unnamed: R35.1, R36.2, U52.3
unnamed: C194.2, DS18.12, TP124.P$1
unnamed: D19.A, L19.P$2, U55.1
unnamed: R37.1, R38.2, U55.3
unnamed: C205.2, DS19.12, TP131.P$1
unnamed: D20.A, L20.P$2, U58.1
unnamed: R39.1, R40.2, U58.3
unnamed: C216.2, DS20.12, TP138.P$1
unnamed: D21.A, L21.P$2, U61.1
unnamed: R41.1, R42.2, U61.3
unnamed: C227.2, DS21.12, TP145.P$1
unnamed: D22.A, L22.P$2, U64.1
unnamed: R43.1, R44.2, U64.3
unnamed: C238.2, DS22.12, TP152.P$1
unnamed: D23.A, L23.P$2, U67.1
unnamed: R45.1, R46.2, U67.3
unnamed: C249.2, DS23.12, TP159.P$1
unnamed: D24.A, L24.P$2, U70.1
unnamed: R47.1, R48.2, U70.3
unnamed: C260.2, DS24.12, TP166.P$1
unnamed: D25.A, L25.P$2, U73.1
unnamed: R49.1, R50.2, U73.3
unnamed: C271.2, DS25.12, TP173.P$1
unnamed: D26.A, L26.P$2, U76.1
unnamed: R51.1, R52.2, U76.3
unnamed: C282.2, DS26.12, TP180.P$1
unnamed: D27.A, L27.P$2, U79.1
unnamed: R53.1, R54.2, U79.3
unnamed: C293.2, DS27.12, TP187.P$1
unnamed: D28.A, L28.P$2, U82.1
unnamed: R55.1, R56.2, U82.3
unnamed: C304.2, DS28.12, TP194.P$1
unnamed: D29.A, L29.P$2, U85.1
unnamed: R57.1, R58.2, U85.3
unnamed: C315.2, DS29.12, TP201.P$1
unnamed: D30.A, L30.P$2, U88.1
unnamed: R59.1, R60.2, U88.3
unnamed: C326.2, DS30.12, TP208.P$1
unnamed: D31.A, L31.P$2, U91.1
unnamed: R61.1, R62.2, U91.3
unnamed: C337.2, DS31.12, TP215.P$1
unnamed: D32.A, L32.P$2, U94.1
unnamed: R63.1, R64.2, U94.3
unnamed: C348.2, DS32.12, TP222.P$1
unnamed: D33.A, L33.P$2, U97.1
unnamed: R65.1, R66.2, U97.3
unnamed: C359.2, DS33.12, TP229.P$1
unnamed: D34.A, L34.P$2, U100.1
unnamed: R67.1, R68.2, U100.3
unnamed: C370.2, DS34.12, TP236.P$1
unnamed: D35.A, L35.P$2, U103.1
unnamed: R69.1, R70.2, U103.3
unnamed: C381.2, DS35.12, TP243.P$1
unnamed: D36.A, L36.P$2, U106.1
unnamed: R71.1, R72.2, U106.3
unnamed: C392.2, DS36.12, TP250.P$1
unnamed: D37.A, L37.P$2, U109.1
unnamed: R73.1, R74.2, U109.3
unnamed: C403.2, DS37.12, TP257.P$1
unnamed: D38.A, L38.P$2, U112.1
unnamed: R75.1, R76.2, U112.3
unnamed: C414.2, DS38.12, TP264.P$1
unnamed: D39.A, L39.P$2, U115.1
unnamed: R77.1, R78.2, U115.3
unnamed: C425.2, DS39.12, TP271.P$1
unnamed: D40.A, L40.P$2, U118.1
unnamed: R79.1, R80.2, U118.3
unnamed: C436.2, DS40.12, TP278.P$1
unnamed: D41.A, L41.P$2, U121.1
unnamed: R81.1, R82.2, U121.3
unnamed: C447.2, DS41.12, TP285.P$1
unnamed: D42.A, L42.P$2, U124.1
unnamed: R83.1, R84.2, U124.3
unnamed: C458.2, DS42.12, TP292.P$1
SCLK: DS1.6, TP3.P$1, U3.4
SCLK1: DS2.6, TP10.P$1, U6.4
SCLK2: DS3.6, TP17.P$1, U9.4
SCLK3: DS4.6, TP24.P$1, U12.4
SCLK4: DS5.6, TP31.P$1, U15.4
SCLK5: DS6.6, TP38.P$1, U18.4
SCLK6: DS7.6, TP45.P$1, U21.4
SCLK7: DS8.6, TP52.P$1, U24.4
SCLK8: DS9.6, TP59.P$1, U27.4
SCLK9: DS10.6, TP66.P$1, U30.4
SCLK10: DS11.6, TP73.P$1, U33.4
SCLK11: DS12.6, TP80.P$1, U36.4
SCLK12: DS13.6, TP87.P$1, U39.4
SCLK13: DS14.6, TP94.P$1, U42.4
SCLK14: DS15.6, TP101.P$1, U45.4
SCLK15: DS16.6, TP108.P$1, U48.4
SCLK16: DS17.6, TP115.P$1, U51.4
SCLK17: DS18.6, TP122.P$1, U54.4
SCLK18: DS19.6, TP129.P$1, U57.4
SCLK19: DS20.6, TP136.P$1, U60.4
SCLK20: DS21.6, TP143.P$1, U63.4
SCLK21: DS22.6, TP150.P$1, U66.4
SCLK22: DS23.6, TP157.P$1, U69.4
SCLK23: DS24.6, TP164.P$1, U72.4
SCLK24: DS25.6, TP171.P$1, U75.4
SCLK25: DS26.6, TP178.P$1, U78.4
SCLK26: DS27.6, TP185.P$1, U81.4
SCLK27: DS28.6, TP192.P$1, U84.4
SCLK28: DS29.6, TP199.P$1, U87.4
SCLK29: DS30.6, TP206.P$1, U90.4
SCLK30: DS31.6, TP213.P$1, U93.4
SCLK31: DS32.6, TP220.P$1, U96.4
SCLK32: DS33.6, TP227.P$1, U99.4
SCLK33: DS34.6, TP234.P$1, U102.4
SCLK34: DS35.6, TP241.P$1, U105.4
SCLK35: DS36.6, TP248.P$1, U108.4
SCLK36: DS37.6, TP255.P$1, U111.4
SCLK37: DS38.6, TP262.P$1, U114.4
SCLK38: DS39.6, TP269.P$1, U117.4
SCLK39: DS40.6, TP276.P$1, U120.4
SCLK40: DS41.6, TP283.P$1, U123.4
SCLK41: DS42.6, TP290.P$1, U126.4
SCLK_HIGH: J2.2, U3.11
SCLK_HIGH1: J1.2, U6.11
SCLK_HIGH2: J3.2, U9.11
SCLK_HIGH3: J4.2, U12.11
SCLK_HIGH4: J5.2, U15.11
SCLK_HIGH5: J6.2, U18.11
SCLK_HIGH6: J7.2, U21.11
SCLK_HIGH7: J8.2, U24.11
SCLK_HIGH8: J9.2, U27.11
SCLK_HIGH9: J10.2, U30.11
SCLK_HIGH10: J11.2, U33.11
SCLK_HIGH11: J12.2, U36.11
SCLK_HIGH12: J13.2, U39.11
SCLK_HIGH13: J14.2, U42.11
SCLK_HIGH14: J15.2, U45.11
SCLK_HIGH15: J16.2, U48.11
SCLK_HIGH16: J17.2, U51.11
SCLK_HIGH17: J18.2, U54.11
SCLK_HIGH18: J19.2, U57.11
SCLK_HIGH19: J20.2, U60.11
SCLK_HIGH20: J21.2, U63.11
SCLK_HIGH21: J22.2, U66.11
SCLK_HIGH22: J23.2, U69.11
SCLK_HIGH23: J24.2, U72.11
SCLK_HIGH24: J25.2, U75.11
SCLK_HIGH25: J26.2, U78.11
SCLK_HIGH26: J27.2, U81.11
SCLK_HIGH27: J28.2, U84.11
SCLK_HIGH28: J29.2, U87.11
SCLK_HIGH29: J30.2, U90.11
SCLK_HIGH30: J31.2, U93.11
SCLK_HIGH31: J32.2, U96.11
SCLK_HIGH32: J33.2, U99.11
SCLK_HIGH33: J34.2, U102.11
SCLK_HIGH34: J35.2, U105.11
SCLK_HIGH35: J36.2, U108.11
SCLK_HIGH36: J37.2, U111.11
SCLK_HIGH37: J38.2, U114.11
SCLK_HIGH38: J39.2, U117.11
SCLK_HIGH39: J40.2, U120.11
SCLK_HIGH40: J41.2, U123.11
SCLK_HIGH41: J42.2, U126.11
SDIN: DS1.7, TP4.P$1, U3.2
SDIN1: DS2.7, TP11.P$1, U6.2
SDIN2: DS3.7, TP18.P$1, U9.2
SDIN3: DS4.7, TP25.P$1, U12.2
SDIN4: DS5.7, TP32.P$1, U15.2
SDIN5: DS6.7, TP39.P$1, U18.2
SDIN6: DS7.7, TP46.P$1, U21.2
SDIN7: DS8.7, TP53.P$1, U24.2
SDIN8: DS9.7, TP60.P$1, U27.2
SDIN9: DS10.7, TP67.P$1, U30.2
SDIN10: DS11.7, TP74.P$1, U33.2
SDIN11: DS12.7, TP81.P$1, U36.2
SDIN12: DS13.7, TP88.P$1, U39.2
SDIN13: DS14.7, TP95.P$1, U42.2
SDIN14: DS15.7, TP102.P$1, U45.2
SDIN15: DS16.7, TP109.P$1, U48.2
SDIN16: DS17.7, TP116.P$1, U51.2
SDIN17: DS18.7, TP123.P$1, U54.2
SDIN18: DS19.7, TP130.P$1, U57.2
SDIN19: DS20.7, TP137.P$1, U60.2
SDIN20: DS21.7, TP144.P$1, U63.2
SDIN21: DS22.7, TP151.P$1, U66.2
SDIN22: DS23.7, TP158.P$1, U69.2
SDIN23: DS24.7, TP165.P$1, U72.2
SDIN24: DS25.7, TP172.P$1, U75.2
SDIN25: DS26.7, TP179.P$1, U78.2
SDIN26: DS27.7, TP186.P$1, U81.2
SDIN27: DS28.7, TP193.P$1, U84.2
SDIN28: DS29.7, TP200.P$1, U87.2
SDIN29: DS30.7, TP207.P$1, U90.2
SDIN30: DS31.7, TP214.P$1, U93.2
SDIN31: DS32.7, TP221.P$1, U96.2
SDIN32: DS33.7, TP228.P$1, U99.2
SDIN33: DS34.7, TP235.P$1, U102.2
SDIN34: DS35.7, TP242.P$1, U105.2
SDIN35: DS36.7, TP249.P$1, U108.2
SDIN36: DS37.7, TP256.P$1, U111.2
SDIN37: DS38.7, TP263.P$1, U114.2
SDIN38: DS39.7, TP270.P$1, U117.2
SDIN39: DS40.7, TP277.P$1, U120.2
SDIN40: DS41.7, TP284.P$1, U123.2
SDIN41: DS42.7, TP291.P$1, U126.2
SDIN_HIGH: J2.3, U3.13
SDIN_HIGH1: J1.3, U6.13
SDIN_HIGH2: J3.3, U9.13
SDIN_HIGH3: J4.3, U12.13
SDIN_HIGH4: J5.3, U15.13
SDIN_HIGH5: J6.3, U18.13
SDIN_HIGH6: J7.3, U21.13
SDIN_HIGH7: J8.3, U24.13
SDIN_HIGH8: J9.3, U27.13
SDIN_HIGH9: J10.3, U30.13
SDIN_HIGH10: J11.3, U33.13
SDIN_HIGH11: J12.3, U36.13
SDIN_HIGH12: J13.3, U39.13
SDIN_HIGH13: J14.3, U42.13
SDIN_HIGH14: J15.3, U45.13
SDIN_HIGH15: J16.3, U48.13
SDIN_HIGH16: J17.3, U51.13
SDIN_HIGH17: J18.3, U54.13
SDIN_HIGH18: J19.3, U57.13
SDIN_HIGH19: J20.3, U60.13
SDIN_HIGH20: J21.3, U63.13
SDIN_HIGH21: J22.3, U66.13
SDIN_HIGH22: J23.3, U69.13
SDIN_HIGH23: J24.3, U72.13
SDIN_HIGH24: J25.3, U75.13
SDIN_HIGH25: J26.3, U78.13
SDIN_HIGH26: J27.3, U81.13
SDIN_HIGH27: J28.3, U84.13
SDIN_HIGH28: J29.3, U87.13
SDIN_HIGH29: J30.3, U90.13
SDIN_HIGH30: J31.3, U93.13
SDIN_HIGH31: J32.3, U96.13
SDIN_HIGH32: J33.3, U99.13
SDIN_HIGH33: J34.3, U102.13
SDIN_HIGH34: J35.3, U105.13
SDIN_HIGH35: J36.3, U108.13
SDIN_HIGH36: J37.3, U111.13
SDIN_HIGH37: J38.3, U114.13
SDIN_HIGH38: J39.3, U117.13
SDIN_HIGH39: J40.3, U120.13
SDIN_HIGH40: J41.3, U123.13
SDIN_HIGH41: J42.3, U126.13
VIN: C1.1, C8.1, C11.1, J2.6, L1.P$1, U1.4, U1.5, U2.1, U2.3, U3.14
VIN1: C12.1, C19.1, C22.1, J1.6, L2.P$1, U4.4, U4.5, U5.1, U5.3, U6.14
VIN2: C23.1, C30.1, C33.1, J3.6, L3.P$1, U7.4, U7.5, U8.1, U8.3, U9.14
VIN3: C34.1, C41.1, C44.1, J4.6, L4.P$1, U10.4, U10.5, U11.1, U11.3, U12.14
VIN4: C45.1, C52.1, C55.1, J5.6, L5.P$1, U13.4, U13.5, U14.1, U14.3, U15.14
VIN5: C56.1, C63.1, C66.1, J6.6, L6.P$1, U16.4, U16.5, U17.1, U17.3, U18.14
VIN6: C67.1, C74.1, C77.1, J7.6, L7.P$1, U19.4, U19.5, U20.1, U20.3, U21.14
VIN7: C78.1, C85.1, C88.1, J8.6, L8.P$1, U22.4, U22.5, U23.1, U23.3, U24.14
VIN8: C89.1, C96.1, C99.1, J9.6, L9.P$1, U25.4, U25.5, U26.1, U26.3, U27.14
VIN9: C100.1, C107.1, C110.1, J10.6, L10.P$1, U28.4, U28.5, U29.1, U29.3, U30.14
VIN10: C111.1, C118.1, C121.1, J11.6, L11.P$1, U31.4, U31.5, U32.1, U32.3, U33.14
VIN11: C122.1, C129.1, C132.1, J12.6, L12.P$1, U34.4, U34.5, U35.1, U35.3, U36.14
VIN12: C133.1, C140.1, C143.1, J13.6, L13.P$1, U37.4, U37.5, U38.1, U38.3, U39.14
VIN13: C144.1, C151.1, C154.1, J14.6, L14.P$1, U40.4, U40.5, U41.1, U41.3, U42.14
VIN14: C155.1, C162.1, C165.1, J15.6, L15.P$1, U43.4, U43.5, U44.1, U44.3, U45.14
VIN15: C166.1, C173.1, C176.1, J16.6, L16.P$1, U46.4, U46.5, U47.1, U47.3, U48.14
VIN16: C177.1, C184.1, C187.1, J17.6, L17.P$1, U49.4, U49.5, U50.1, U50.3, U51.14
VIN17: C188.1, C195.1, C198.1, J18.6, L18.P$1, U52.4, U52.5, U53.1, U53.3, U54.14
VIN18: C199.1, C206.1, C209.1, J19.6, L19.P$1, U55.4, U55.5, U56.1, U56.3, U57.14
VIN19: C210.1, C217.1, C220.1, J20.6, L20.P$1, U58.4, U58.5, U59.1, U59.3, U60.14
VIN20: C221.1, C228.1, C231.1, J21.6, L21.P$1, U61.4, U61.5, U62.1, U62.3, U63.14
VIN21: C232.1, C239.1, C242.1, J22.6, L22.P$1, U64.4, U64.5, U65.1, U65.3, U66.14
VIN22: C243.1, C250.1, C253.1, J23.6, L23.P$1, U67.4, U67.5, U68.1, U68.3, U69.14
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
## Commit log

2018-02-21 Cleaning up repo added version number
2018-02-21 Fixed issue with multiple boards
2018-02-21 fixed consistency issue
2018-02-23 post design review/checklist changes
2018-02-23 post QC checklist changes
2018-03-08 added panel
2018-03-12 post checklist changes
2018-03-22 created panel v10
2018-05-10 changed prod_id on inductor
2018-05-29 cleaned repo
